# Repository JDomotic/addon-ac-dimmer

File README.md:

# AC Dimmer Addon
This is a custom made 2 channel AC dimmer addon which fits on the back of the [Wireless sensor board](https://github.com/JDomotic/esp12-wireless-sensor-board) .

The board can receive commands over uart with configurable transition speed per channel. 
It also has a 230VAC button input and a 230VAC power meter

## Version 1 | 05-01-2019
**Features**:
* Onboard 1A 3.3v AC power supply
* Zero cross detection 
* Two triac for 230VAC dimming with a total power of 4 amps (or 2*2 amps)
* Input for a 230VAC button 
* 230VAC power meter  
* Small formfactor, fits in electric wall boxes 

**Schematic**

**BOM**

**Ref**|**Qnty**|**Value**|**Footprint**|**Vendor (LCSC)**
:-----: | :-----: | :-----: | :-----: | :-----:
C1,|1|1nF|Capacitor\_SMD:C\_1206\_3216Metric\_Pad1.42x1.75mm\_HandSolder|C152975
C2,|1|10uF/10V|Capacitor\_THT:CP\_Radial\_D4.0mm\_P2.00mm|C191532
C7,|1|0.1uf|Capacitor\_SMD:C\_1206\_3216Metric\_Pad1.42x1.75mm\_HandSolder|C128353
C8,|1|100nF 450v|Capacitor\_SMD:C\_1206\_3216Metric\_Pad1.42x1.75mm\_HandSolder|C106025
D1,|1|1N4148|Diode\_SMD:D\_SOD-123|C184882
D2,|1|MB6S|Package\_TO\_SOT\_SMD:TO-269AA|C83867
F1,|1|Glass fuse 10mm 4A|Resistor\_THT:R\_Axial\_DIN0411\_L9.9mm\_D3.6mm\_P12.70mm\_Horizontal|C140492
J1,|1|Screw\_Terminal\_01x05|TerminalBlock\_RND:TerminalBlock\_RND\_205-00279\_1x05\_P5.00mm\_Vertical|C163149
J1,|1|Screw\_Terminal\_01x05|TerminalBlock\_RND:TerminalBlock\_RND\_205-00279\_1x05\_P5.00mm\_Vertical|C163148
J2,|1|Conn\_01x02\_Male ZMCT|Connector\_PinHeader\_2.54mm:PinHeader\_1x02\_P2.54mm\_Vertical|-
J3,|1|Conn\_01x05\_Male|Connector\_PinHeader\_2.54mm:PinHeader\_1x05\_P2.54mm\_Vertical|-
J4,|1|Conn\_01x05\_Male RIGHT|Connector\_PinHeader\_2.54mm:PinHeader\_1x05\_P2.54mm\_Vertical|-
J5,|1|Programm header|Connector\_PinHeader\_2.54mm:PinHeader\_1x04\_P2.54mm\_Vertical|-
Q1, Q2,|2|BT136-600D|Package\_TO\_SOT\_THT:TO-220-3\_Vertical|C130426
Q1, Q2,|2|TO-220 heatsink|TO-220 heatsink|C4650
Q5,|1|2N3904|Package\_TO\_SOT\_SMD:SOT-23|C18536
R1, R2, R16, R17,|4|180 0.25W 200v|Resistor\_SMD:R\_1210\_3225Metric\_Pad1.42x2.65mm\_HandSolder|C171148
R3, R4, R12,|3|100|Resistor\_SMD:R\_0805\_2012Metric\_Pad1.15x1.40mm\_HandSolder|-
R5,|1|4.7K|Resistor\_SMD:R\_0805\_2012Metric\_Pad1.15x1.40mm\_HandSolder|C328399
R6, R7,|2|220K 0.25W 200v|Resistor\_SMD:R\_0805\_2012Metric\_Pad1.15x1.40mm\_HandSolder|C352118
R8, R11, R13,|3|1K|Resistor\_SMD:R\_0805\_2012Metric\_Pad1.15x1.40mm\_HandSolder|C95781
R9,|1|22K|Resistor\_SMD:R\_0805\_2012Metric\_Pad1.15x1.40mm\_HandSolder|-
R10,|1|1K|Resistor\_SMD:R\_1206\_3216Metric\_Pad1.30x1.75mm\_HandSolder|C175514
R14,|1|10K|Resistor\_SMD:R\_0805\_2012Metric\_Pad1.15x1.40mm\_HandSolder|C103904
R15,|1|DNS|Resistor\_SMD:R\_0805\_2012Metric\_Pad1.15x1.40mm\_HandSolder|C103904
U1,|1|HLK-PM02|Power\_Supply:HLK-PM03| 
U2, U3,|2|MOC3052|Package\_DIP:SMDIP-6\_W7.62mm|C115471
U4,|1|4N35|Package\_DIP:SMDIP-6\_W7.62mm|C115444
U6,|1|ATTINY414-SSNR|Package\_SO:SOIC-14\_3.9x8.7mm\_P1.27mm|C189365
U7,|1|H11AA1SM|Package\_DIP:SMDIP-6\_W7.62mm|C184383

**Render**

**Assembled**

Assembeled with 1 triac (lower height):

Assembeled with 2 triacs:

**Issues**

There are a few issues with the board: 
1. The wrong SOT-23 footprint is used. Due this, the transistor Q5 needs to be soldered upside down (This because pin 1 and 2 are flipped) 
2. R14 and R5 references are swapped on the PCB silkscreen. 
3. Due a fault in the schematic, the button input cannot work. To fix this, leg number 6 of U7 must be cut off and pad 5 and 6 should be soldered together.

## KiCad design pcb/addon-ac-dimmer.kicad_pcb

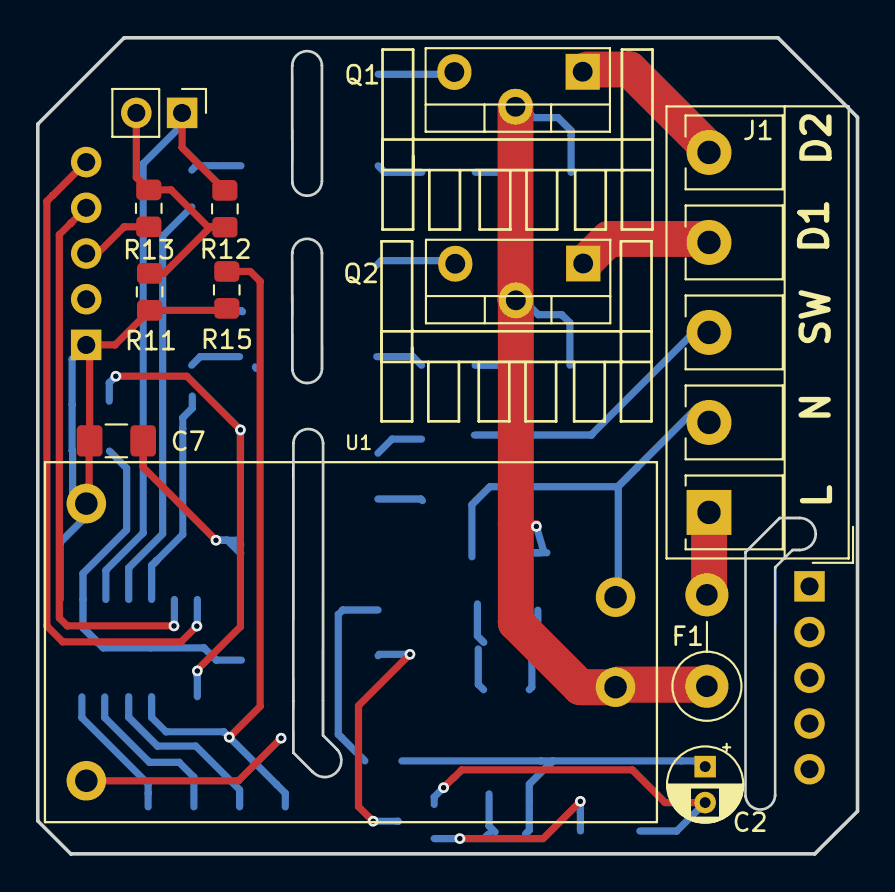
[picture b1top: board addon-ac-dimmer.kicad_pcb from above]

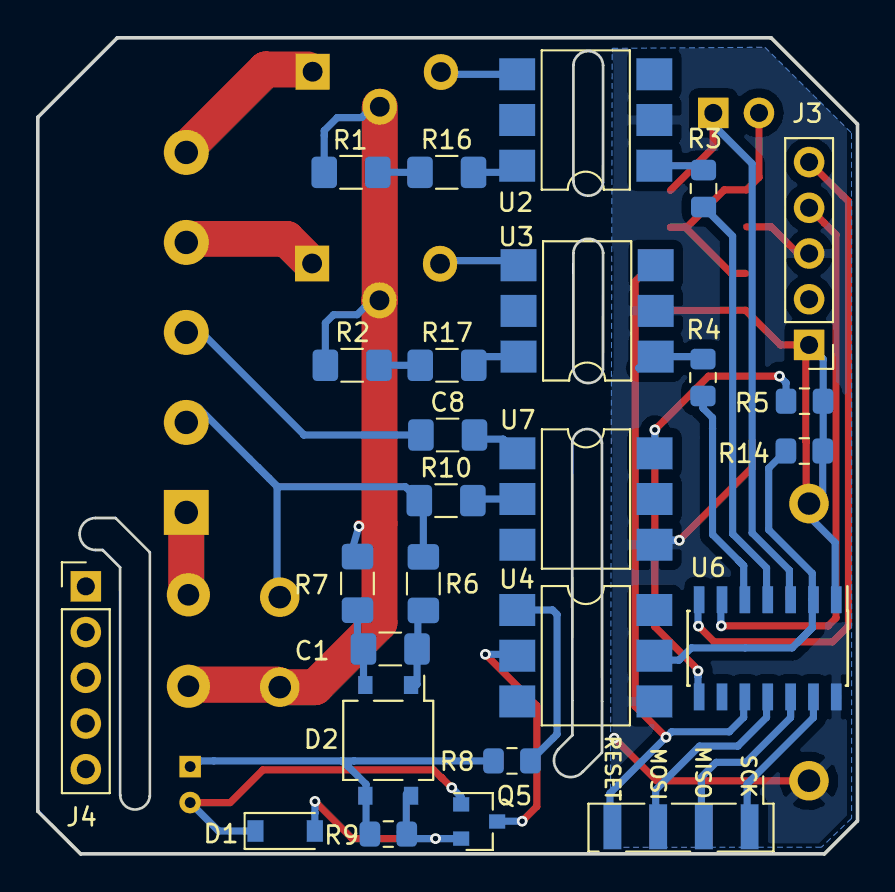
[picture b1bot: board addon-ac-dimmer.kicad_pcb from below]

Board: 2 copper layers, 45.5 x 45.3 mm, 38 parts (26 on the bottom side), 37 nets.

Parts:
C1: 1nF; C_1206_3216Metric_Pad1.42x1.75mm_HandSolder
C2: 10uF/10V; CP_Radial_D4.0mm_P2.00mm
C7: 0.1uf; C_1206_3216Metric_Pad1.42x1.75mm_HandSolder
C8: 100nF; C_1206_3216Metric_Pad1.42x1.75mm_HandSolder
D1: 1N4148; D_SOD-123
D2: MB6S; TO-269AA
F1: Glass fuse 10mm 4A; R_Axial_DIN0411_L9.9mm_D3.6mm_P5.08mm_Vertical
J1: Screw_Terminal_01x05; TerminalBlock_RND_205-00279_1x05_P5.00mm_Vertical
J2: Conn_01x02_Male ZMCT; PinHeader_1x02_P2.54mm_Vertical
J3: Conn_01x05_Male; PinHeader_1x05_P2.54mm_Vertical
J4: Conn_01x05_Male RIGHT; PinHeader_1x05_P2.54mm_Vertical
J5: Programm header; PinHeader_1x04_P2.54mm_Vertical_SMD_Pin1Left
Q1, Q2: BT136-600D; TO-220-3_Vertical
Q5: 2N3904; SOT-23
R1, R16: 180; R_1206_3216Metric_Pad1.42x1.75mm_HandSolder
R2, R17: 360; R_1206_3216Metric_Pad1.42x1.75mm_HandSolder
R3, R4: 100; R_0805_2012Metric_Pad1.15x1.40mm_HandSolder
R5: 4.7K; R_0805_2012Metric_Pad1.15x1.40mm_HandSolder
R6, R7: 220K; R_1206_3216Metric_Pad1.42x1.75mm_HandSolder
R8, R11, R13: 1K; R_0805_2012Metric_Pad1.15x1.40mm_HandSolder
R9: 22K; R_0805_2012Metric_Pad1.15x1.40mm_HandSolder
R10: 1K; R_1206_3216Metric_Pad1.42x1.75mm_HandSolder
R12: 50; R_0805_2012Metric_Pad1.15x1.40mm_HandSolder
R14, R15: 10K; R_0805_2012Metric_Pad1.15x1.40mm_HandSolder
U1: HLK-PM02; HLK-PM03
U2, U3: MOC3052; SMDIP-6_W7.62mm
U4: 4N35; SMDIP-6_W7.62mm
U6: ATTINY414-SSNR; SOIC-14_3.9x8.7mm_P1.27mm
U7: H11AA1SM; SMDIP-6_W7.62mm

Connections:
+3V3: C7.2, J3.1, R5.1, R11.2, R14.2, R15.2, U1.4, U6.1
GND: C7.1, J3.3, R13.1, U1.3, U2.2, U3.2, U4.4, U6.14, U7.4
LINE: F1.1, Q1.2, Q2.2, R1.2, R2.2, R7.2, U1.1
NEUT: J1.2, R6.2, R10.1, U1.2
unnamed: C1.1, D2.1, R6.1
unnamed: C1.2, D2.2, R7.1
unnamed: C2.1, D2.3, R8.2, R9.1
unnamed: C2.2, D1.1, Q5.1
unnamed: C8.2, U7.1
unnamed: D1.2, D2.4, Q5.2, R9.2
unnamed: F1.2, J1.1
unnamed: J1.4, Q2.1
unnamed: J1.5, Q1.1
unnamed: J2.1, R12.2, U6.3
unnamed: J2.2, R11.1, R12.1, R13.2
unnamed: J3.4, U6.6
unnamed: J3.5, U6.7
unnamed: J5.1, U6.13
unnamed: J5.2, U6.12
unnamed: J5.3, U6.11
unnamed: J5.4, R15.1, U6.10
unnamed: Q1.3, U2.4
unnamed: Q2.3, U3.4
unnamed: Q5.3, U4.2
unnamed: R1.1, R16.1
unnamed: R3.1, U6.4
unnamed: R3.2, U2.1
unnamed: R4.1, U6.5
unnamed: R4.2, U3.1
unnamed: R5.2, U4.5, U6.2
unnamed: R8.1, U4.1
unnamed: R10.2, U7.2
unnamed: R14.1, U6.8, U7.6
unnamed: R16.2, U2.6
unnamed: R2.1, R17.1
unnamed: R17.2, U3.6
SW_1_LINE: C8.1, J1.3

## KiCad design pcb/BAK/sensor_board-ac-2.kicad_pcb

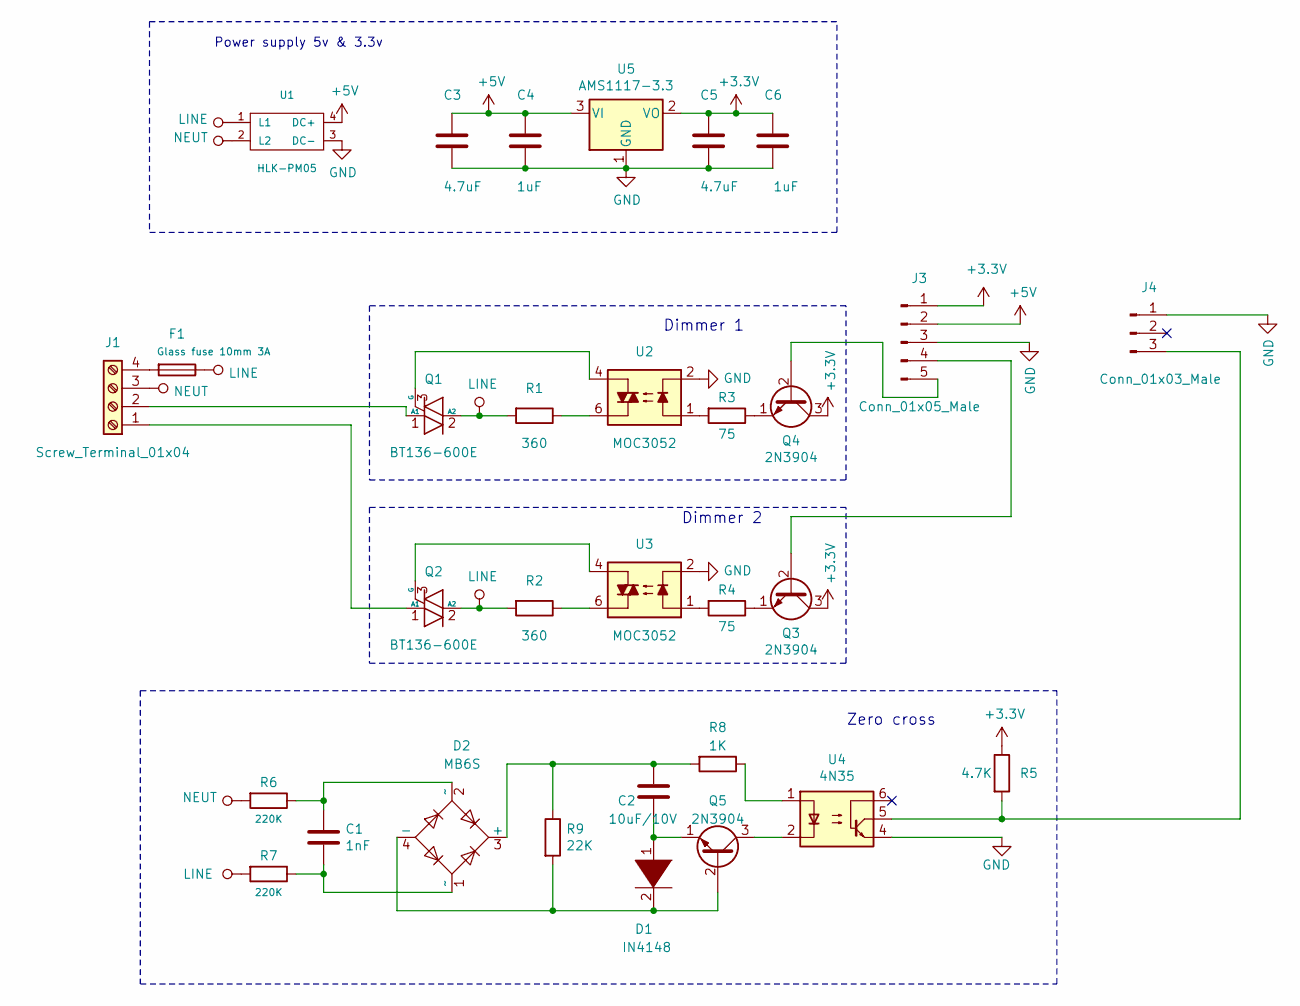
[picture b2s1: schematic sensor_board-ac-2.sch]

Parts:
C1: 1nF; C_1206_3216Metric_Pad1.42x1.75mm_HandSolder
C2: 10uF/10V; CP_Radial_D4.0mm_P2.00mm
C3, C5: 4.7uF; C_1206_3216Metric_Pad1.42x1.75mm_HandSolder
C4, C6: 1uF; C_1206_3216Metric_Pad1.42x1.75mm_HandSolder
D1: IN4148; D_SOD-123
D2: MB6S; TO-269AA
F1: Glass fuse 10mm 3A; R_Axial_DIN0411_L9.9mm_D3.6mm_P5.08mm_Vertical
J1: Screw_Terminal_01x04; TerminalBlock_RND_205-00278_1x04_P5.00mm_Vertical
J3: Conn_01x05_Male; PinHeader_1x05_P2.54mm_Vertical
J4: Conn_01x03_Male; PinHeader_1x03_P2.54mm_Vertical
Q1, Q2: BT136-600E; TO-220-3_Vertical
Q3, Q4, Q5: 2N3904; TO-92_Inline_Wide
R1, R2: 360; R_1210_3225Metric_Pad1.42x2.65mm_HandSolder
R3, R4: 75; R_0805_2012Metric_Pad1.15x1.40mm_HandSolder
R5: 4.7K; R_0805_2012Metric_Pad1.15x1.40mm_HandSolder
R6, R7: 220K; R_0805_2012Metric_Pad1.15x1.40mm_HandSolder
R8: 1K; R_0805_2012Metric_Pad1.15x1.40mm_HandSolder
R9: 22K; R_0805_2012Metric_Pad1.15x1.40mm_HandSolder
U1: HLK-PM05; HLK-PM03
U2, U3: MOC3052; DIP-6_W7.62mm
U4: 4N35; DIP-6_W7.62mm
U5: AMS1117-3.3; SOT-223-3_TabPin2

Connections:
+3V3: C5.1, C6.1, J3.1, Q3.3 (C), Q4.3 (C), R5.1, U5.2 (VO)
+5V: C3.1, C4.1, J3.2, U1.4 (DC+), U5.3 (VI)
GND: C3.2, C4.2, C5.2, C6.2, J3.3, J4.1, U1.3 (DC-), U2.2, U3.2, U4.4, U5.1 (GND)
LINE: F1.1, Q1.2 (A2), Q2.2 (A2), R1.2, R2.2, R7.2, U1.1 (L1)
NEUT: J1.3, R6.2, U1.2 (L2)
unnamed: C1.1, D2.2 (~~), R6.1
unnamed: C1.2, D2.1 (~~), R7.1
unnamed: C2.1, D2.3 (+), R8.2, R9.1
unnamed: C2.2, D1.1 (K), Q5.1 (E)
unnamed: D1.2 (A), D2.4 (-), Q5.2 (B), R9.2
unnamed: F1.2, J1.4
unnamed: J1.1, Q2.1 (A1)
unnamed: J1.2, Q1.1 (A1)
unnamed: J3.4, Q3.2 (B)
unnamed: J3.5, Q4.2 (B)
unnamed: J4.3, R5.2, U4.5
unnamed: Q1.3 (G), U2.4
unnamed: Q2.3 (G), U3.4
unnamed: Q3.1 (E), R4.1
unnamed: Q4.1 (E), R3.1
unnamed: Q5.3 (C), U4.2
unnamed: R1.1, U2.6
unnamed: R2.1, U3.6
unnamed: R3.2, U2.1
unnamed: R4.2, U3.1
unnamed: R8.1, U4.1

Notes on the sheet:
Dimmer 1
Dimmer 2
Zero cross
Power supply 5v & 3.3v

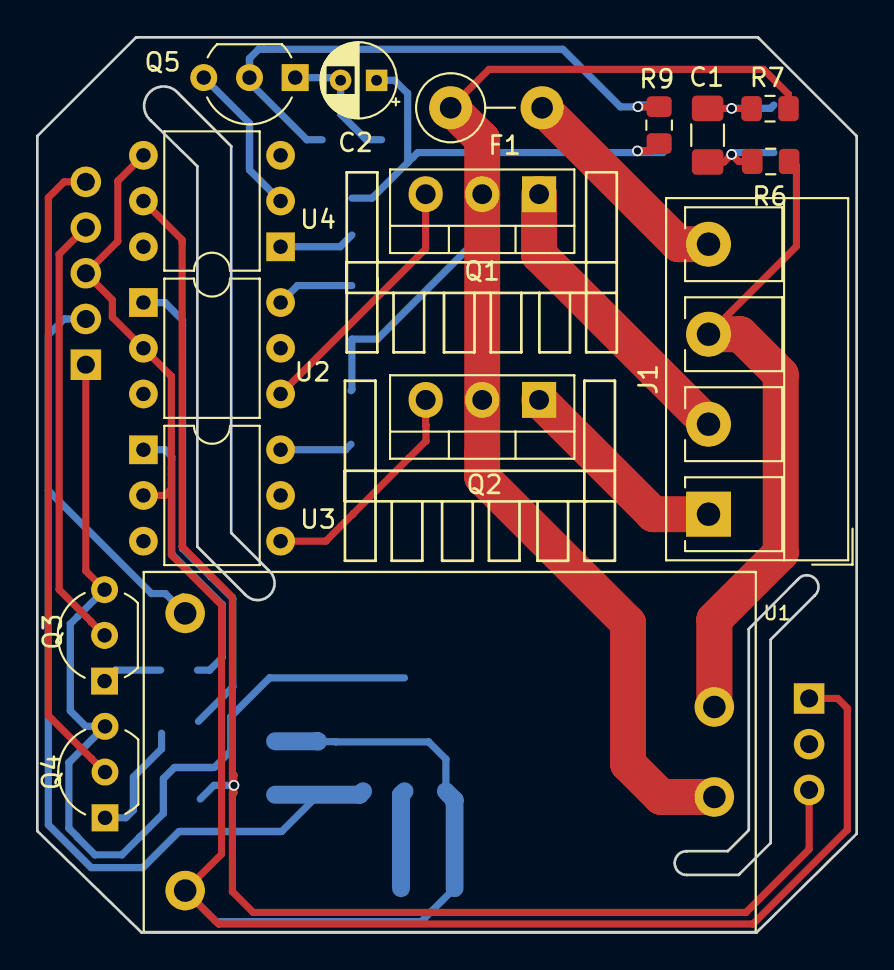
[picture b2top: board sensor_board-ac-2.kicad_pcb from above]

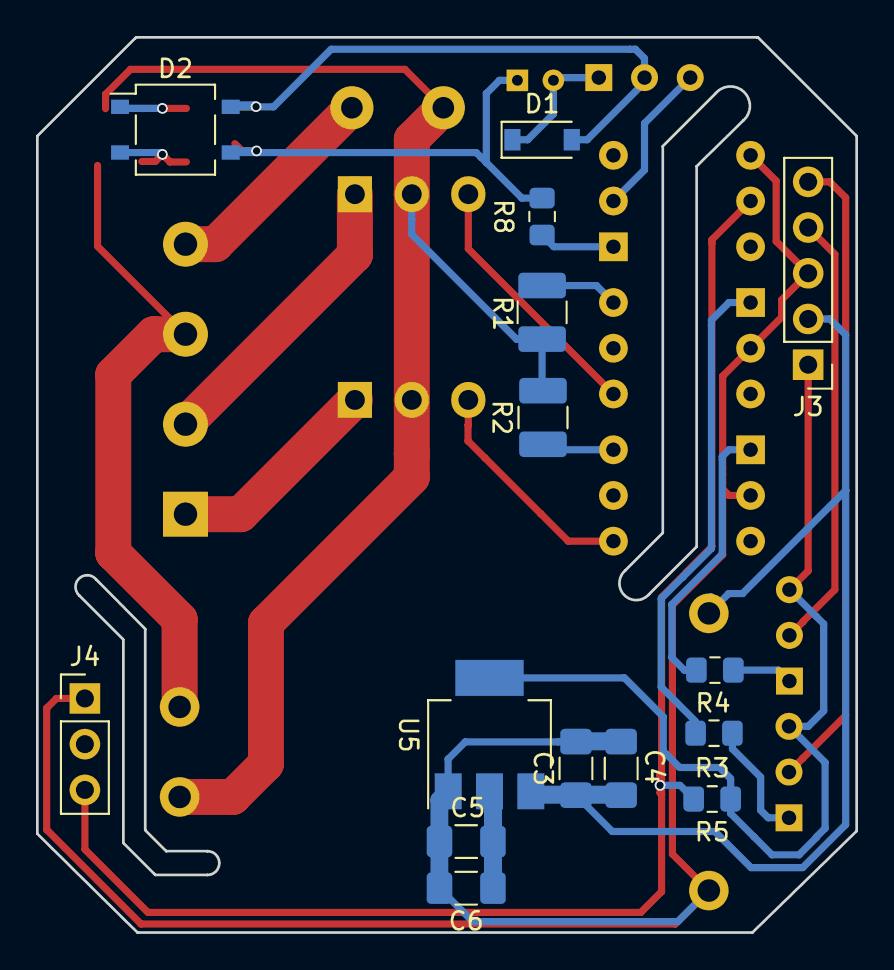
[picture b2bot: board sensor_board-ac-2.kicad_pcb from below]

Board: 2 copper layers, 45.5 x 49.7 mm, 31 parts (15 on the bottom side), 26 nets.

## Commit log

2021-01-15 Init
2021-01-17 Repository cleanup
2021-01-17 Add readfme
